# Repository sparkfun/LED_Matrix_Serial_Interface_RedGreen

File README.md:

LED Matrix Serial Interface-Red/Green
======================================

[  
*LED Matrix- Serial Interface- Red/Green (COM-00759)*](https://www.sparkfun.com/products/759)

This is a medium sized LED Matrix with a backpack that has been designed to take SPI serial input and display any graphics you pass it.

Repository Contents
-------------------
* **/Firmware** - Firmware that comes installed on the backpack
* **/Hardware** - All Eagle design files (.brd, .sch)

License Information
-------------------
The hardware is released under [Creative Commons Share-alike 3.0](http://creativecommons.org/licenses/by-sa/3.0/).  
All other code is open source so please feel free to do anything you want with it; you buy me a beer if you use this and we meet someday ([Beerware license](http://en.wikipedia.org/wiki/Beerware)).

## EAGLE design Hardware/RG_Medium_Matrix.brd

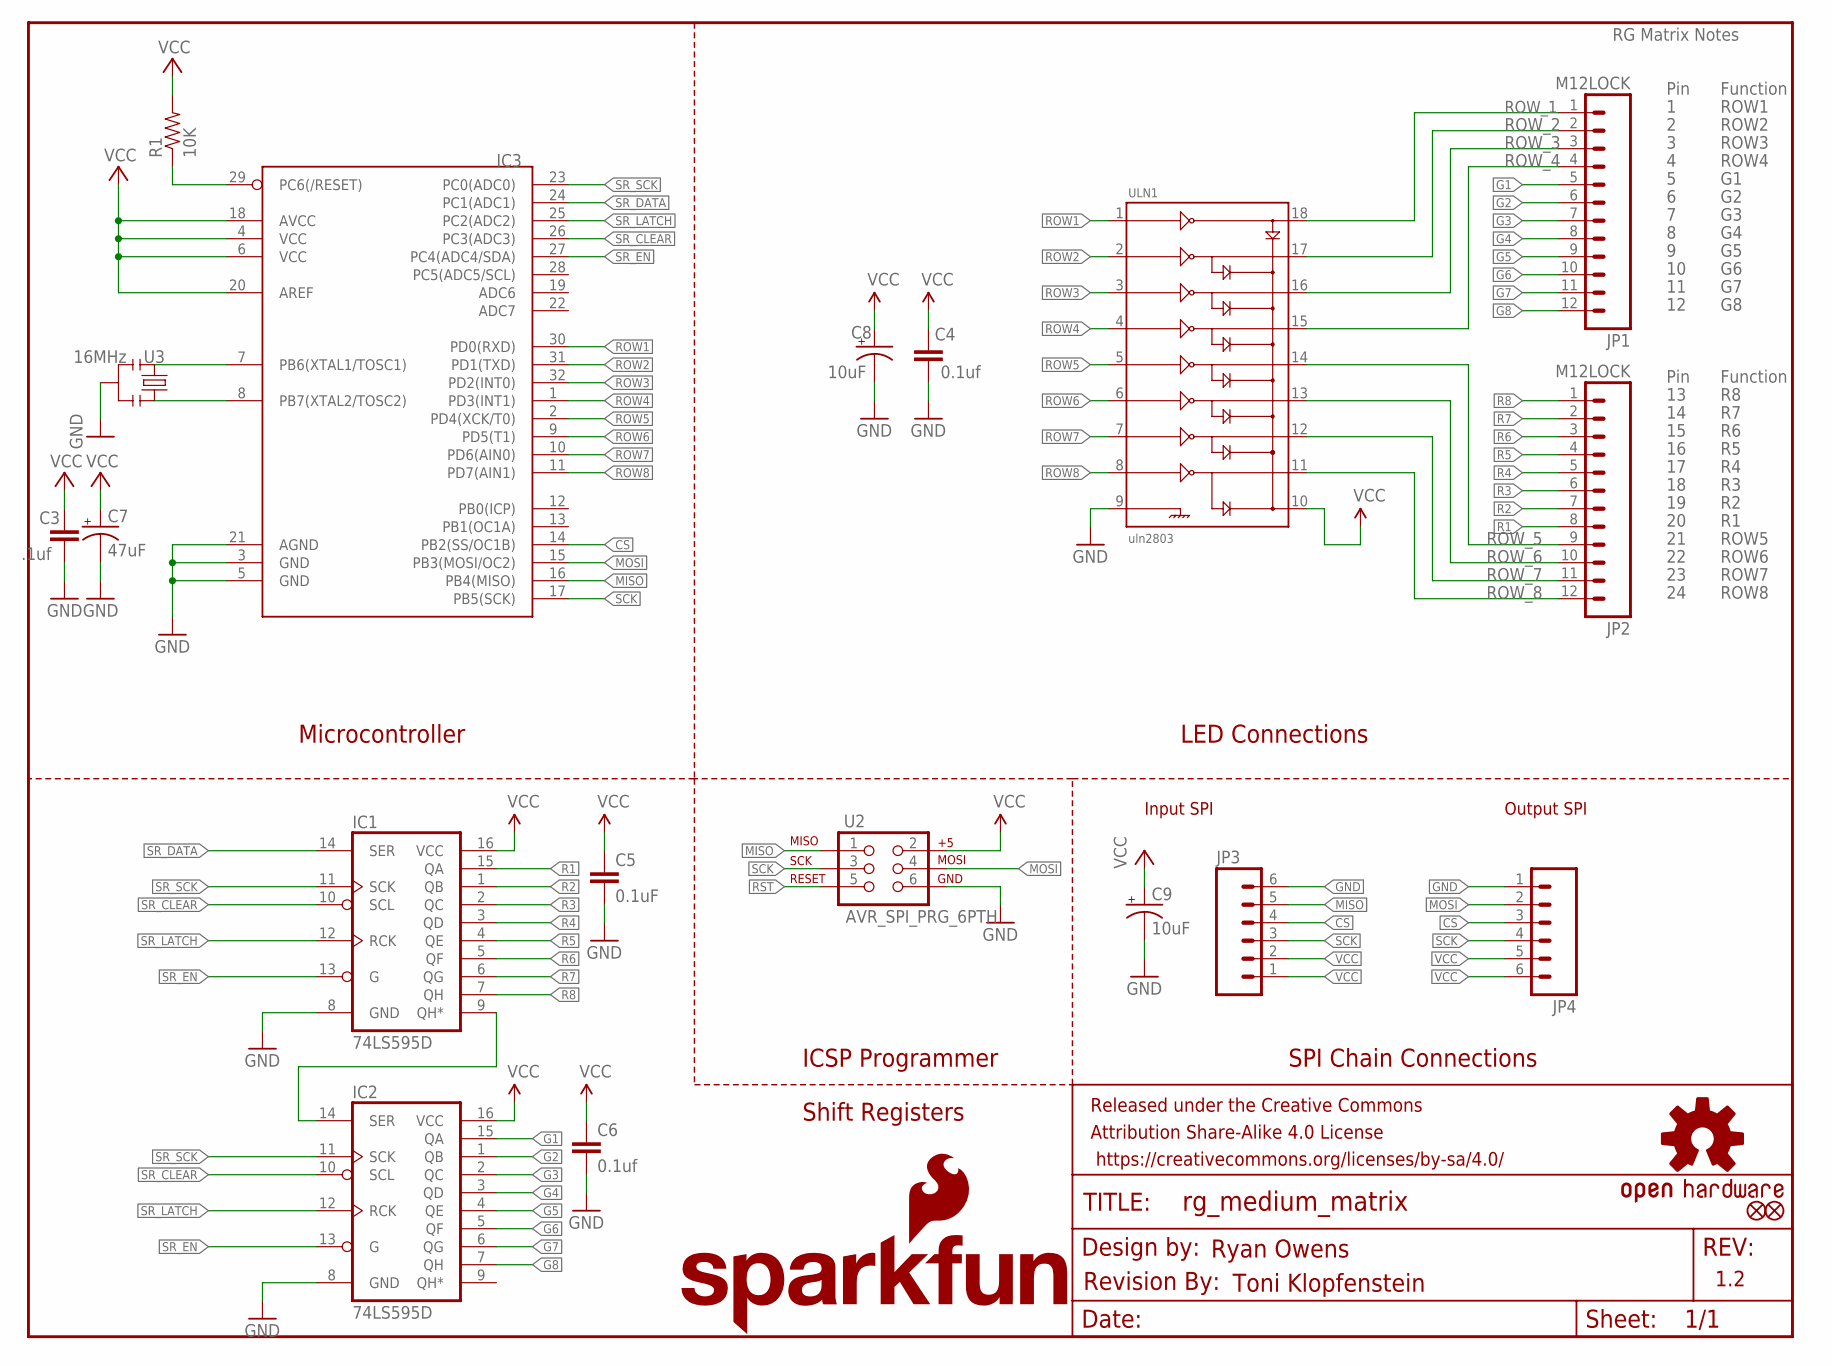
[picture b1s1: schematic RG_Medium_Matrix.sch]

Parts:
C3: .1uf; 0603-CAP
C4, C6: 0.1uf; 0603-CAP
C5: 0.1uF; 0603-CAP
C7: 47uF; EIA3528
C8, C9: 10uF; EIA3216
FRAME1: FRAME-LETTER; CREATIVE_COMMONS
IC1, IC2: 74LS595D; SO16
IC3: ATMEGA328_SMT; TQFP32-08
JP1, JP2: M12LOCK; 1X12_LOCK
JP3, JP4: M06LOCK; 1X06_LOCK
LOGO1: OSHW-LOGOS; OSHW-LOGO-S
LOGO2: SFE_LOGO_NAME_FLAME.1_INCH; SFE_LOGO_NAME_FLAME_.1
R1: 10K; 0603-RES
U2: AVR_SPI_PRG_6PTH; 2X3
U3: 16MHz; RESONATOR-SMD
U$1, U$3: FIDUCIAL1X2; FIDUCIAL-1X2
U$2: REVISION
ULN1: uln2803; SO18L

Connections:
CS: IC3.14 (PB2(SS/OC1B)), JP3.4, JP4.3
G1: IC2.15 (QA), JP1.5
G2: IC2.1 (QB), JP1.6
G3: IC2.2 (QC), JP1.7
G4: IC2.3 (QD), JP1.8
G5: IC2.4 (QE), JP1.9
G6: IC2.5 (QF), JP1.10
G7: IC2.6 (QG), JP1.11
G8: IC2.7 (QH), JP1.12
GND: C3.2, C4.1, C5.2, C6.2, C7.C (-), C8.C (-), C9.C (-), IC1.8 (GND), IC2.8 (GND), IC3.3 (GND), IC3.5 (GND), IC3.21 (AGND), JP3.6, JP4.1, U2.6, U3.2, ULN1.9
MISO: IC3.16 (PB4(MISO)), JP3.5, U2.1
MOSI: IC3.15 (PB3(MOSI/OC2)), JP4.2, U2.4
unnamed: IC3.7 (PB6(XTAL1/TOSC1)), U3.1
unnamed: IC3.8 (PB7(XTAL2/TOSC2)), U3.3
unnamed: IC1.9 (QH*), IC2.14 (SER)
R1: IC1.15 (QA), JP2.8
R2: IC1.1 (QB), JP2.7
R3: IC1.2 (QC), JP2.6
R4: IC1.3 (QD), JP2.5
R5: IC1.4 (QE), JP2.4
R6: IC1.5 (QF), JP2.3
R7: IC1.6 (QG), JP2.2
R8: IC1.7 (QH), JP2.1
ROW1: IC3.30 (PD0(RXD)), ULN1.1
ROW2: IC3.31 (PD1(TXD)), ULN1.2
ROW3: IC3.32 (PD2(INT0)), ULN1.3
ROW4: IC3.1 (PD3(INT1)), ULN1.4
ROW5: IC3.2 (PD4(XCK/T0)), ULN1.5
ROW6: IC3.9 (PD5(T1)), ULN1.6
ROW7: IC3.10 (PD6(AIN0)), ULN1.7
ROW8: IC3.11 (PD7(AIN1)), ULN1.8
ROW_1: JP1.1, ULN1.18
ROW_2: JP1.2, ULN1.17
ROW_3: JP1.3, ULN1.16
ROW_4: JP1.4, ULN1.15
ROW_5: JP2.9, ULN1.14
ROW_6: JP2.10, ULN1.13
ROW_7: JP2.11, ULN1.12
ROW_8: JP2.12, ULN1.11
RST: IC3.29 (PC6(/RESET)), R1.1, U2.5
SCK: IC3.17 (PB5(SCK)), JP3.3, JP4.4, U2.3
SR_CLEAR: IC1.10 (SCL), IC2.10 (SCL), IC3.26 (PC3(ADC3))
SR_DATA: IC1.14 (SER), IC3.24 (PC1(ADC1))
SR_EN: IC1.13 (G), IC2.13 (G), IC3.27 (PC4(ADC4/SDA))
SR_LATCH: IC1.12 (RCK), IC2.12 (RCK), IC3.25 (PC2(ADC2))
SR_SCK: IC1.11 (SCK), IC2.11 (SCK), IC3.23 (PC0(ADC0))
VCC: C3.1, C4.2, C5.1, C6.1, C7.A (+), C8.A (+), C9.A (+), IC1.16 (VCC), IC2.16 (VCC), IC3.4 (VCC), IC3.6 (VCC), IC3.18 (AVCC), IC3.20 (AREF), JP3.1, JP3.2, JP4.5, JP4.6, R1.2, U2.2, ULN1.10

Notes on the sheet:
1.2
Pin
Function
ROW1
ROW2
ROW3
ROW4
ROW5
ROW6
ROW7
ROW8
RG Matrix Notes
Input SPI
Output SPI
Toni Klopfenstein
Ryan Owens
Microcontroller
LED Connections
ICSP Programmer
Shift Registers
SPI Chain Connections

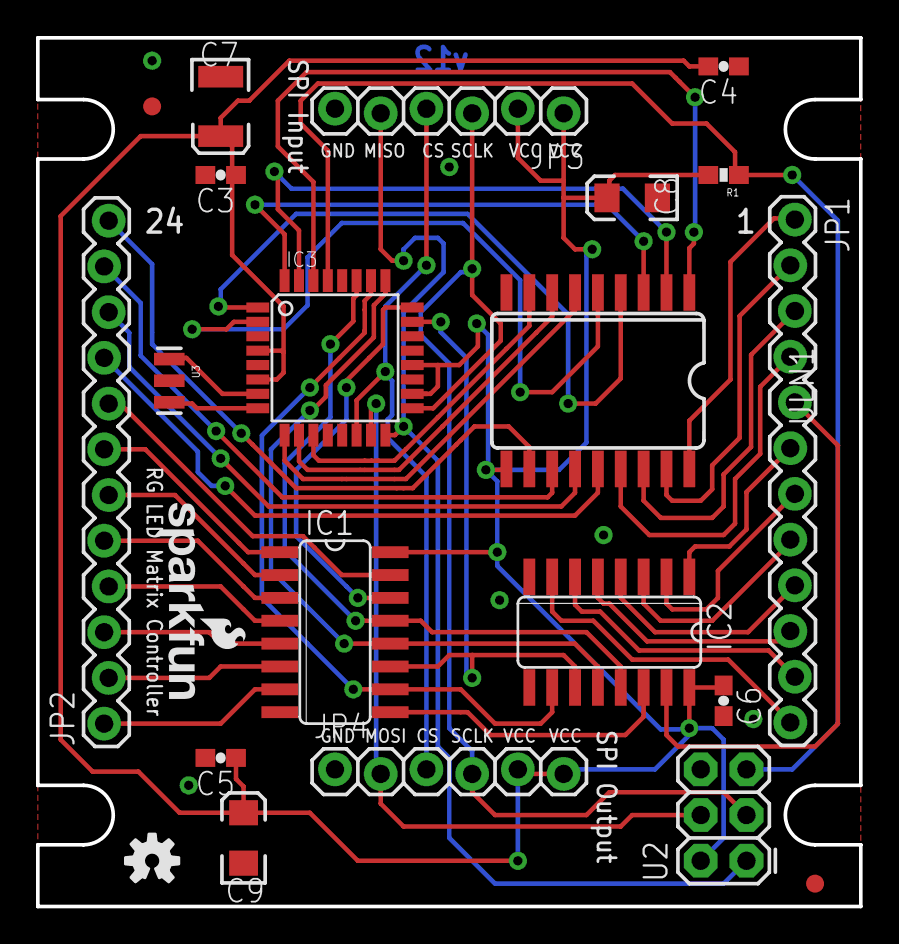
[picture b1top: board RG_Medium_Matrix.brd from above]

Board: 2 copper layers, 45.7 x 48.3 mm, 24 parts (0 on the bottom side), 47 nets.

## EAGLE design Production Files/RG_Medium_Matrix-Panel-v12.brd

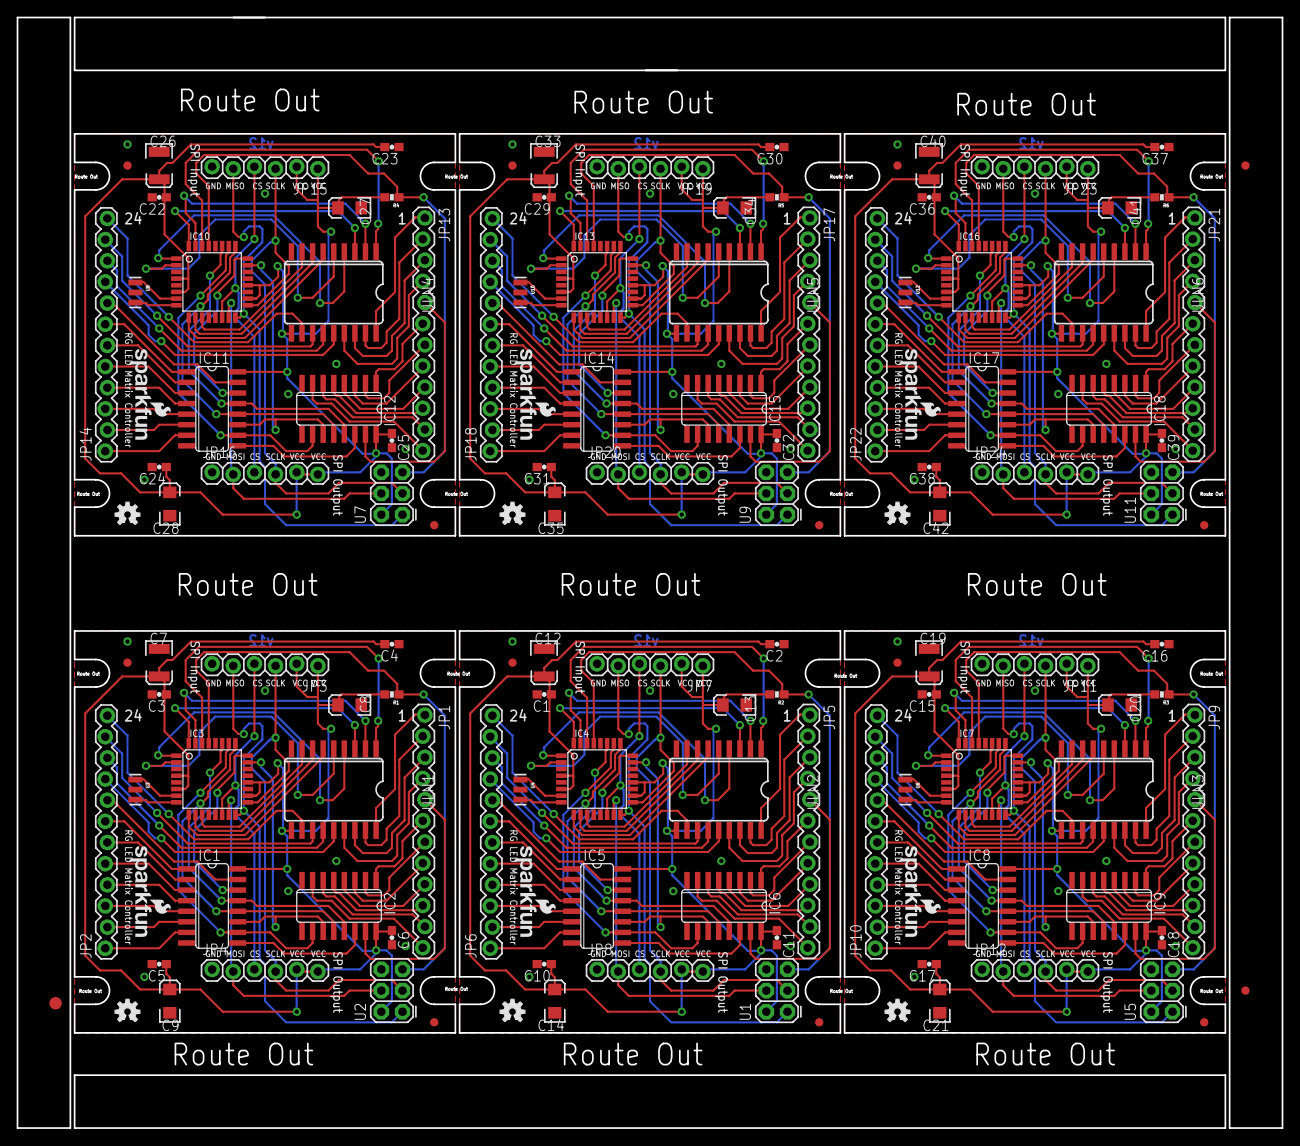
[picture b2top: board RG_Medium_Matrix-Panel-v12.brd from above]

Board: 2 copper layers, 151.9 x 133.3 mm, 135 parts (0 on the bottom side), 282 nets.

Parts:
C1, C3, C15, C22, C29, C36: .1uf; 0603-CAP
C2, C4, C6, C11, C16, C18, C23, C25, C30, C32, C37, C39: 0.1uf; 0603-CAP
C5, C10, C17, C24, C31, C38: 0.1uF; 0603-CAP
C7, C12, C19, C26, C33, C40: 47uF; EIA3528
C8, C9, C13, C14, C20, C21, C27, C28, C34, C35, C41, C42: 10uF; EIA3216
E$1: FIDUCIAL-1.5X3
E$3, E$4: FIDUCIAL-1X2
IC1, IC2, IC5, IC6, IC8, IC9, IC11, IC12, IC14, IC15, IC17, IC18: 74LS595D; SO16
IC3, IC4, IC7, IC10, IC13, IC16: TQFP32-08
JP1, JP2, JP5, JP6, JP9, JP10, JP13, JP14, JP17, JP18, JP21, JP22: M12LOCK; 1X12_LOCK
JP3, JP4, JP7, JP8, JP11, JP12, JP15, JP16, JP19, JP20, JP23, JP24: 1X06_LOCK
LOGO1, LOGO3, LOGO5, LOGO7, LOGO9, LOGO11: OSHW-LOGOS; OSHW-LOGO-S
LOGO2, LOGO4, LOGO6, LOGO8, LOGO10, LOGO12: SFE_LOGO_NAME_FLAME.1_INCH; SFE_LOGO_NAME_FLAME_.1
R1, R2, R3, R4, R5, R6: 10K; 0603-RES
U1, U2, U5, U7, U9, U11: AVR_SPI_PRG_6PTH; 2X3
U3, U4, U6, U8, U10, U12: 16MHz; RESONATOR-SMD
U$1, U$2, U$3, U$4, U$5, U$6, U$7, U$8, U$9, U$10, U$11, U$12: FIDUCIAL1X2; FIDUCIAL-1X2
ULN1, ULN2, ULN3, ULN4, ULN5, ULN6: uln2803; SO18L

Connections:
CS: IC3.14, JP3.4, JP4.3
CS1: IC4.14, JP7.4, JP8.3
CS2: IC7.14, JP11.4, JP12.3
CS3: IC10.14, JP15.4, JP16.3
CS4: IC13.14, JP19.4, JP20.3
CS5: IC16.14, JP23.4, JP24.3
G1: IC2.15, JP1.5
G2: IC2.1, JP1.6
G3: IC2.2, JP1.7
G4: IC2.3, JP1.8
G5: IC2.4, JP1.9
G6: IC2.5, JP1.10
G7: IC2.6, JP1.11
G8: IC2.7, JP1.12
G9: IC6.15, JP5.5
G10: IC6.1, JP5.6
G11: IC6.2, JP5.7
G12: IC6.3, JP5.8
G13: IC6.4, JP5.9
G14: IC6.5, JP5.10
G15: IC6.6, JP5.11
G16: IC6.7, JP5.12
G17: IC9.15, JP9.5
G18: IC9.1, JP9.6
G19: IC9.2, JP9.7
G20: IC9.3, JP9.8
G21: IC9.4, JP9.9
G22: IC9.5, JP9.10
G23: IC9.6, JP9.11
G24: IC9.7, JP9.12
G25: IC12.15, JP13.5
G26: IC12.1, JP13.6
G27: IC12.2, JP13.7
G28: IC12.3, JP13.8
G29: IC12.4, JP13.9
G30: IC12.5, JP13.10
G31: IC12.6, JP13.11
G32: IC12.7, JP13.12
G33: IC15.15, JP17.5
G34: IC15.1, JP17.6
G35: IC15.2, JP17.7
G36: IC15.3, JP17.8
G37: IC15.4, JP17.9
G38: IC15.5, JP17.10
G39: IC15.6, JP17.11
G40: IC15.7, JP17.12
G41: IC18.15, JP21.5
G42: IC18.1, JP21.6
G43: IC18.2, JP21.7
G44: IC18.3, JP21.8
G45: IC18.4, JP21.9
G46: IC18.5, JP21.10
G47: IC18.6, JP21.11
G48: IC18.7, JP21.12
GND: C3.2, C4.1, C5.2, C6.2, C7.C, C8.C, C9.C, IC1.8, IC2.8, IC3.3, IC3.5, IC3.21, JP3.6, JP4.1, U2.6, U3.2, ULN1.9
GND1: C1.2, C2.1, C10.2, C11.2, C12.C, C13.C, C14.C, IC4.3, IC4.5, IC4.21, IC5.8, IC6.8, JP7.6, JP8.1, U1.6, U4.2, ULN2.9
GND2: C15.2, C16.1, C17.2, C18.2, C19.C, C20.C, C21.C, IC7.3, IC7.5, IC7.21, IC8.8, IC9.8, JP11.6, JP12.1, U5.6, U6.2, ULN3.9
GND3: C22.2, C23.1, C24.2, C25.2, C26.C, C27.C, C28.C, IC10.3, IC10.5, IC10.21, IC11.8, IC12.8, JP15.6, JP16.1, U7.6, U8.2, ULN4.9
GND4: C29.2, C30.1, C31.2, C32.2, C33.C, C34.C, C35.C, IC13.3, IC13.5, IC13.21, IC14.8, IC15.8, JP19.6, JP20.1, U9.6, U10.2, ULN5.9
GND5: C36.2, C37.1, C38.2, C39.2, C40.C, C41.C, C42.C, IC16.3, IC16.5, IC16.21, IC17.8, IC18.8, JP23.6, JP24.1, U11.6, U12.2, ULN6.9
MISO: IC3.16, JP3.5, U2.1
MISO1: IC4.16, JP7.5, U1.1
MISO2: IC7.16, JP11.5, U5.1
MISO3: IC10.16, JP15.5, U7.1
MISO4: IC13.16, JP19.5, U9.1
MISO5: IC16.16, JP23.5, U11.1
MOSI: IC3.15, JP4.2, U2.4
MOSI1: IC4.15, JP8.2, U1.4
MOSI2: IC7.15, JP12.2, U5.4
MOSI3: IC10.15, JP16.2, U7.4
MOSI4: IC13.15, JP20.2, U9.4
MOSI5: IC16.15, JP24.2, U11.4
unnamed: IC3.7, U3.1
unnamed: IC3.8, U3.3
unnamed: IC5.9, IC6.14
unnamed: IC4.7, U4.1
unnamed: IC4.8, U4.3
unnamed: IC8.9, IC9.14
unnamed: IC7.7, U6.1
unnamed: IC7.8, U6.3
unnamed: IC11.9, IC12.14
unnamed: IC10.7, U8.1
unnamed: IC10.8, U8.3
unnamed: IC14.9, IC15.14
unnamed: IC13.7, U10.1
unnamed: IC13.8, U10.3
unnamed: IC17.9, IC18.14
unnamed: IC16.7, U12.1
unnamed: IC16.8, U12.3
unnamed: IC1.9, IC2.14
R1: IC1.15, JP2.8
R2: IC1.1, JP2.7
R3: IC1.2, JP2.6
R4: IC1.3, JP2.5
R5: IC1.4, JP2.4
R6: IC1.5, JP2.3
R7: IC1.6, JP2.2
R8: IC1.7, JP2.1
R9: IC5.15, JP6.8
R10: IC5.1, JP6.7
R11: IC5.2, JP6.6
R12: IC5.3, JP6.5
R13: IC5.4, JP6.4
R14: IC5.5, JP6.3
R15: IC5.6, JP6.2
R16: IC5.7, JP6.1
R17: IC8.15, JP10.8
R18: IC8.1, JP10.7
R19: IC8.2, JP10.6
R20: IC8.3, JP10.5
R21: IC8.4, JP10.4
R22: IC8.5, JP10.3
R23: IC8.6, JP10.2
R24: IC8.7, JP10.1
R25: IC11.15, JP14.8
R26: IC11.1, JP14.7
R27: IC11.2, JP14.6
R28: IC11.3, JP14.5
R29: IC11.4, JP14.4
R30: IC11.5, JP14.3
R31: IC11.6, JP14.2
R32: IC11.7, JP14.1
R33: IC14.15, JP18.8
R34: IC14.1, JP18.7
R35: IC14.2, JP18.6
R36: IC14.3, JP18.5
R37: IC14.4, JP18.4
R38: IC14.5, JP18.3
R39: IC14.6, JP18.2
R40: IC14.7, JP18.1
R41: IC17.15, JP22.8
R42: IC17.1, JP22.7
R43: IC17.2, JP22.6
R44: IC17.3, JP22.5
R45: IC17.4, JP22.4
R46: IC17.5, JP22.3
R47: IC17.6, JP22.2
R48: IC17.7, JP22.1
ROW1: IC3.30, ULN1.1
ROW2: IC3.31, ULN1.2
ROW3: IC3.32, ULN1.3
ROW4: IC3.1, ULN1.4
ROW5: IC3.2, ULN1.5
ROW6: IC3.9, ULN1.6
ROW7: IC3.10, ULN1.7
ROW8: IC3.11, ULN1.8
ROW9: IC4.30, ULN2.1
ROW10: IC4.31, ULN2.2
ROW11: IC4.32, ULN2.3
ROW12: IC4.1, ULN2.4
ROW13: IC4.2, ULN2.5
ROW14: IC4.9, ULN2.6
ROW15: IC4.10, ULN2.7
ROW16: IC4.11, ULN2.8
ROW17: IC7.30, ULN3.1
ROW18: IC7.31, ULN3.2
ROW19: IC7.32, ULN3.3
ROW20: IC7.1, ULN3.4
ROW21: IC7.2, ULN3.5
ROW22: IC7.9, ULN3.6
ROW23: IC7.10, ULN3.7
ROW24: IC7.11, ULN3.8
ROW25: IC10.30, ULN4.1
ROW26: IC10.31, ULN4.2
ROW27: IC10.32, ULN4.3
ROW28: IC10.1, ULN4.4
ROW29: IC10.2, ULN4.5
ROW30: IC10.9, ULN4.6
ROW31: IC10.10, ULN4.7
ROW32: IC10.11, ULN4.8
ROW33: IC13.30, ULN5.1
ROW34: IC13.31, ULN5.2
ROW35: IC13.32, ULN5.3
ROW36: IC13.1, ULN5.4
ROW37: IC13.2, ULN5.5
ROW38: IC13.9, ULN5.6
ROW39: IC13.10, ULN5.7
ROW40: IC13.11, ULN5.8
ROW41: IC16.30, ULN6.1
ROW42: IC16.31, ULN6.2
ROW43: IC16.32, ULN6.3
ROW44: IC16.1, ULN6.4
ROW45: IC16.2, ULN6.5
ROW46: IC16.9, ULN6.6
ROW47: IC16.10, ULN6.7
ROW48: IC16.11, ULN6.8
ROW_1: JP1.1, ULN1.18
ROW_2: JP1.2, ULN1.17
ROW_3: JP1.3, ULN1.16
ROW_4: JP1.4, ULN1.15
ROW_5: JP2.9, ULN1.14
ROW_6: JP2.10, ULN1.13
ROW_7: JP2.11, ULN1.12
ROW_8: JP2.12, ULN1.11
ROW_9: JP5.1, ULN2.18
ROW_10: JP5.2, ULN2.17
ROW_11: JP5.3, ULN2.16
ROW_12: JP5.4, ULN2.15
ROW_13: JP6.9, ULN2.14
ROW_14: JP6.10, ULN2.13
ROW_15: JP6.11, ULN2.12
ROW_16: JP6.12, ULN2.11
ROW_17: JP9.1, ULN3.18
ROW_18: JP9.2, ULN3.17
ROW_19: JP9.3, ULN3.16
ROW_20: JP9.4, ULN3.15
ROW_21: JP10.9, ULN3.14
ROW_22: JP10.10, ULN3.13
ROW_23: JP10.11, ULN3.12
ROW_24: JP10.12, ULN3.11
ROW_25: JP13.1, ULN4.18
ROW_26: JP13.2, ULN4.17
ROW_27: JP13.3, ULN4.16
ROW_28: JP13.4, ULN4.15
ROW_29: JP14.9, ULN4.14
ROW_30: JP14.10, ULN4.13
ROW_31: JP14.11, ULN4.12
ROW_32: JP14.12, ULN4.11
ROW_33: JP17.1, ULN5.18
ROW_34: JP17.2, ULN5.17
ROW_35: JP17.3, ULN5.16
ROW_36: JP17.4, ULN5.15
ROW_37: JP18.9, ULN5.14
ROW_38: JP18.10, ULN5.13
ROW_39: JP18.11, ULN5.12
ROW_40: JP18.12, ULN5.11
ROW_41: JP21.1, ULN6.18
ROW_42: JP21.2, ULN6.17
ROW_43: JP21.3, ULN6.16
ROW_44: JP21.4, ULN6.15
ROW_45: JP22.9, ULN6.14
ROW_46: JP22.10, ULN6.13
ROW_47: JP22.11, ULN6.12
ROW_48: JP22.12, ULN6.11
RST: IC3.29, R1.1, U2.5
RST1: IC4.29, R2.1, U1.5
RST2: IC7.29, R3.1, U5.5
RST3: IC10.29, R4.1, U7.5
RST4: IC13.29, R5.1, U9.5
RST5: IC16.29, R6.1, U11.5
SCK: IC3.17, JP3.3, JP4.4, U2.3
SCK1: IC4.17, JP7.3, JP8.4, U1.3
SCK2: IC7.17, JP11.3, JP12.4, U5.3
SCK3: IC10.17, JP15.3, JP16.4, U7.3
SCK4: IC13.17, JP19.3, JP20.4, U9.3
SCK5: IC16.17, JP23.3, JP24.4, U11.3
SR_CLEAR: IC1.10, IC2.10, IC3.26
SR_CLEAR1: IC4.26, IC5.10, IC6.10
SR_CLEAR2: IC7.26, IC8.10, IC9.10
SR_CLEAR3: IC10.26, IC11.10, IC12.10
SR_CLEAR4: IC13.26, IC14.10, IC15.10
SR_CLEAR5: IC16.26, IC17.10, IC18.10
SR_DATA: IC1.14, IC3.24
SR_DATA1: IC4.24, IC5.14
SR_DATA2: IC7.24, IC8.14
SR_DATA3: IC10.24, IC11.14
SR_DATA4: IC13.24, IC14.14
SR_DATA5: IC16.24, IC17.14
SR_EN: IC1.13, IC2.13, IC3.27
SR_EN1: IC4.27, IC5.13, IC6.13
SR_EN2: IC7.27, IC8.13, IC9.13
SR_EN3: IC10.27, IC11.13, IC12.13
SR_EN4: IC13.27, IC14.13, IC15.13
SR_EN5: IC16.27, IC17.13, IC18.13
SR_LATCH: IC1.12, IC2.12, IC3.25
SR_LATCH1: IC4.25, IC5.12, IC6.12
SR_LATCH2: IC7.25, IC8.12, IC9.12
SR_LATCH3: IC10.25, IC11.12, IC12.12
SR_LATCH4: IC13.25, IC14.12, IC15.12
SR_LATCH5: IC16.25, IC17.12, IC18.12
SR_SCK: IC1.11, IC2.11, IC3.23
SR_SCK1: IC4.23, IC5.11, IC6.11
SR_SCK2: IC7.23, IC8.11, IC9.11
SR_SCK3: IC10.23, IC11.11, IC12.11
SR_SCK4: IC13.23, IC14.11, IC15.11
SR_SCK5: IC16.23, IC17.11, IC18.11
VCC: C3.1, C4.2, C5.1, C6.1, C7.A, C8.A, C9.A, IC1.16, IC2.16, IC3.4, IC3.6, IC3.18, IC3.20, JP3.1, JP3.2, JP4.5, JP4.6, R1.2, U2.2, ULN1.10
VCC1: C1.1, C2.2, C10.1, C11.1, C12.A, C13.A, C14.A, IC4.4, IC4.6, IC4.18, IC4.20, IC5.16, IC6.16, JP7.1, JP7.2, JP8.5, JP8.6, R2.2, U1.2, ULN2.10
VCC2: C15.1, C16.2, C17.1, C18.1, C19.A, C20.A, C21.A, IC7.4, IC7.6, IC7.18, IC7.20, IC8.16, IC9.16, JP11.1, JP11.2, JP12.5, JP12.6, R3.2, U5.2, ULN3.10
VCC3: C22.1, C23.2, C24.1, C25.1, C26.A, C27.A, C28.A, IC10.4, IC10.6, IC10.18, IC10.20, IC11.16, IC12.16, JP15.1, JP15.2, JP16.5, JP16.6, R4.2, U7.2, ULN4.10
VCC4: C29.1, C30.2, C31.1, C32.1, C33.A, C34.A, C35.A, IC13.4, IC13.6, IC13.18, IC13.20, IC14.16, IC15.16, JP19.1, JP19.2, JP20.5, JP20.6, R5.2, U9.2, ULN5.10
VCC5: C36.1, C37.2, C38.1, C39.1, C40.A, C41.A, C42.A, IC16.4, IC16.6, IC16.18, IC16.20, IC17.16, IC18.16, JP23.1, JP23.2, JP24.5, JP24.6, R6.2, U11.2, ULN6.10

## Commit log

2013-08-12 Initial file commit
2014-05-16 Updating to V_1.2- 0603 packages, trace cleaning
2014-05-19 Updating to locking footprints for SPI connectors
2014-05-19 Switching to locking fp for 12 pin headers
2014-07-03 created panel v12
2014-08-05 Moving female header in to reduce gap between screens
2014-08-05 Final update
2014-08-08 re-created panel v12
2014-08-29 re-re-created panel v12
    this panel has proper spacing for male and female headers

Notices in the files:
parts and their libraries:
SparkFun-Aesthetics: Licensing: Creative Commons ShareAlike 4.0 International - https://creativecommons.org/licenses/by-sa/4.0
SparkFun-Aesthetics: Released under the Creative Commons Attribution Share-Alike 4.0 License
SparkFun-Aesthetics: https://creativecommons.org/licenses/by-sa/4.0
